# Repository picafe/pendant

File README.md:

# Bicolor LED Pendant

A pendant built from two PCBs: a 8×8 bicolor LED matrix module (red, orange, green) and controller board with battery charging, USB-C power, 5 V boost, and motion sensing.

## Why I made this

I had already been working on a 32×8 bicolor matrix module and wanted to try the Pendant YSWS before the deadline. An example on the pendant website inspired me to make a bicolor version with an orange fire-style pattern. Fitting the full matrix and controller on one 2/4 layer board was not the most possible, so my design splits into a display PCB and a pendant controller, which are connected with 2.54mm pitch pin headers (likely just male machine pin headers soldered on both sides, since they have a larger spacing to accomodate for the inductor). There is also an accelerometer to have potential particle motion simulation.

## Photos

### 3D model

### Schematic

**Controller**

**Matrix**

### PCB layouts

**Controller board**

**Matrix module**

## Connections

All signals between the two boards are carried on PCB-mounted 2.54 mm pin headers. No off-board wiring is required beyond a LiPo cell on the controller.

## Bill of materials

Prices are per-unit LCSC values; standard connector values are estimated.

### Controller PCB

| Ref | Qty | Value | LCSC | Unit | Extended |
|-----|-----|-------|------|------|----------|
| U3 | 1 | STM32C071G8U6 | C44521811 | $1.67 | $1.67 |
| U4 | 1 | TPS61022 | C915088 | $1.32 | $1.32 |
| U5 | 1 | LIS2DW12TR | C189624 | $1.25 | $1.25 |
| U1 | 1 | XC6206P332MR | C5446 | $0.102 | $0.10 |
| U6 | 1 | TP4056-42-ESOP8 | C16581 | $0.19 | $0.19 |
| L1 | 1 | FXL0530-1R0-M | C475517 | $0.17 | $0.17 |
| Q1, Q2, Q3 | 3 | BSS138W | C28646265 | $0.025 | $0.08 |
| D1 | 1 | BAT54CW | C22392482 | $0.035 | $0.04 |
| D2 | 1 | Red LED | C2286 | $0.009 | $0.01 |
| D3 | 1 | SS34 | C8678 | $0.030 | $0.03 |
| F1 | 1 | SMD1206B150TFT | C269120 | $0.03 | $0.03 |
| S1 | 1 | Tactile button | C720477 | $0.053 | $0.05 |
| J4 | 1 | USB-C receptacle | C18357552 | $0.08 | $0.08 |
| J1 | 1 | JST-SH 4-pin | - | $0.08 *(est.)* | $0.08 |
| J2, J3 | 2 | 4-pin pin socket | - | $0.05 *(est.)* | $0.10 |
| J5 | 1 | 2-pin pin socket | - | $0.03 *(est.)* | $0.03 |
| C9–C13 | 5 | 10 µF | C440198 | $0.069 | $0.35 |
| C1 | 1 | 4.7 µF | C19666 | $0.014 | $0.01 |
| C8 | 1 | 10 µF | C96446 | $0.021 | $0.02 |
| C3, C4, C7 | 3 | 100 nF | C14663 | $0.006 | $0.02 |
| C5 | 1 | 1 µF | C15849 | $0.008 | $0.01 |
| C6 | 1 | 1 µF | C28323 | $0.012 | $0.01 |
| C2 | 1 | 100 nF | C1525 | $0.004 | $0.00 |
| R10–R11, R8–R9 | 4 | 4.7 kΩ | C25900 | $0.004 | $0.02 |
| R4, R5 | 2 | 5.1 kΩ | C25905 | $0.004 | $0.01 |
| R2, R6 | 2 | 100 kΩ | C25741 | $0.004 | $0.01 |
| R1 | 1 | 750 kΩ | C23240 | $0.004 | $0.00 |
| R3 | 1 | 1 kΩ | C11702 | $0.004 | $0.00 |
| R7 | 1 | 10 kΩ | C25804 | $0.004 | $0.00 |
| R12 | 1 | 10 kΩ | C25744 | $0.004 | $0.00 |
| R13 | 1 | 120 Ω | C25079 | $0.004 | $0.00 |

**Controller subtotal: $5.71**

### Matrix PCB

| Ref | Qty | Value | LCSC | Unit | Extended |
|-----|-----|-------|------|------|----------|
| U1 | 1 | HT16K33A-28SSOP | C5444738 | $0.50 | $0.50 |
| LED1 | 1 | 8×8 bicolor LED matrix | - | $1.50 *(est.)* | $1.50 |
| R1–R3 | 3 | 47 kΩ | C25819 | $0.004 | $0.01 |
| C1 | 1 | 100 nF | C14663 | $0.006 | $0.01 |
| D1 | 1 | 1N4148WS | C2128 | $0.012 | $0.01 |
| J1, J2 | 2 | 4-pin pin socket | - | $0.05 *(est.)* | $0.10 |

**Matrix subtotal: $2.13**

### Total component cost

| Board | Subtotal |
|-------|----------|
| Controller | $5.71 |
| Matrix | $2.13 |
| **Grand total (1× each board)** | **$7.84** |

*Does not include PCB fabrication, shipping, LiPo battery, or assembly fees.*

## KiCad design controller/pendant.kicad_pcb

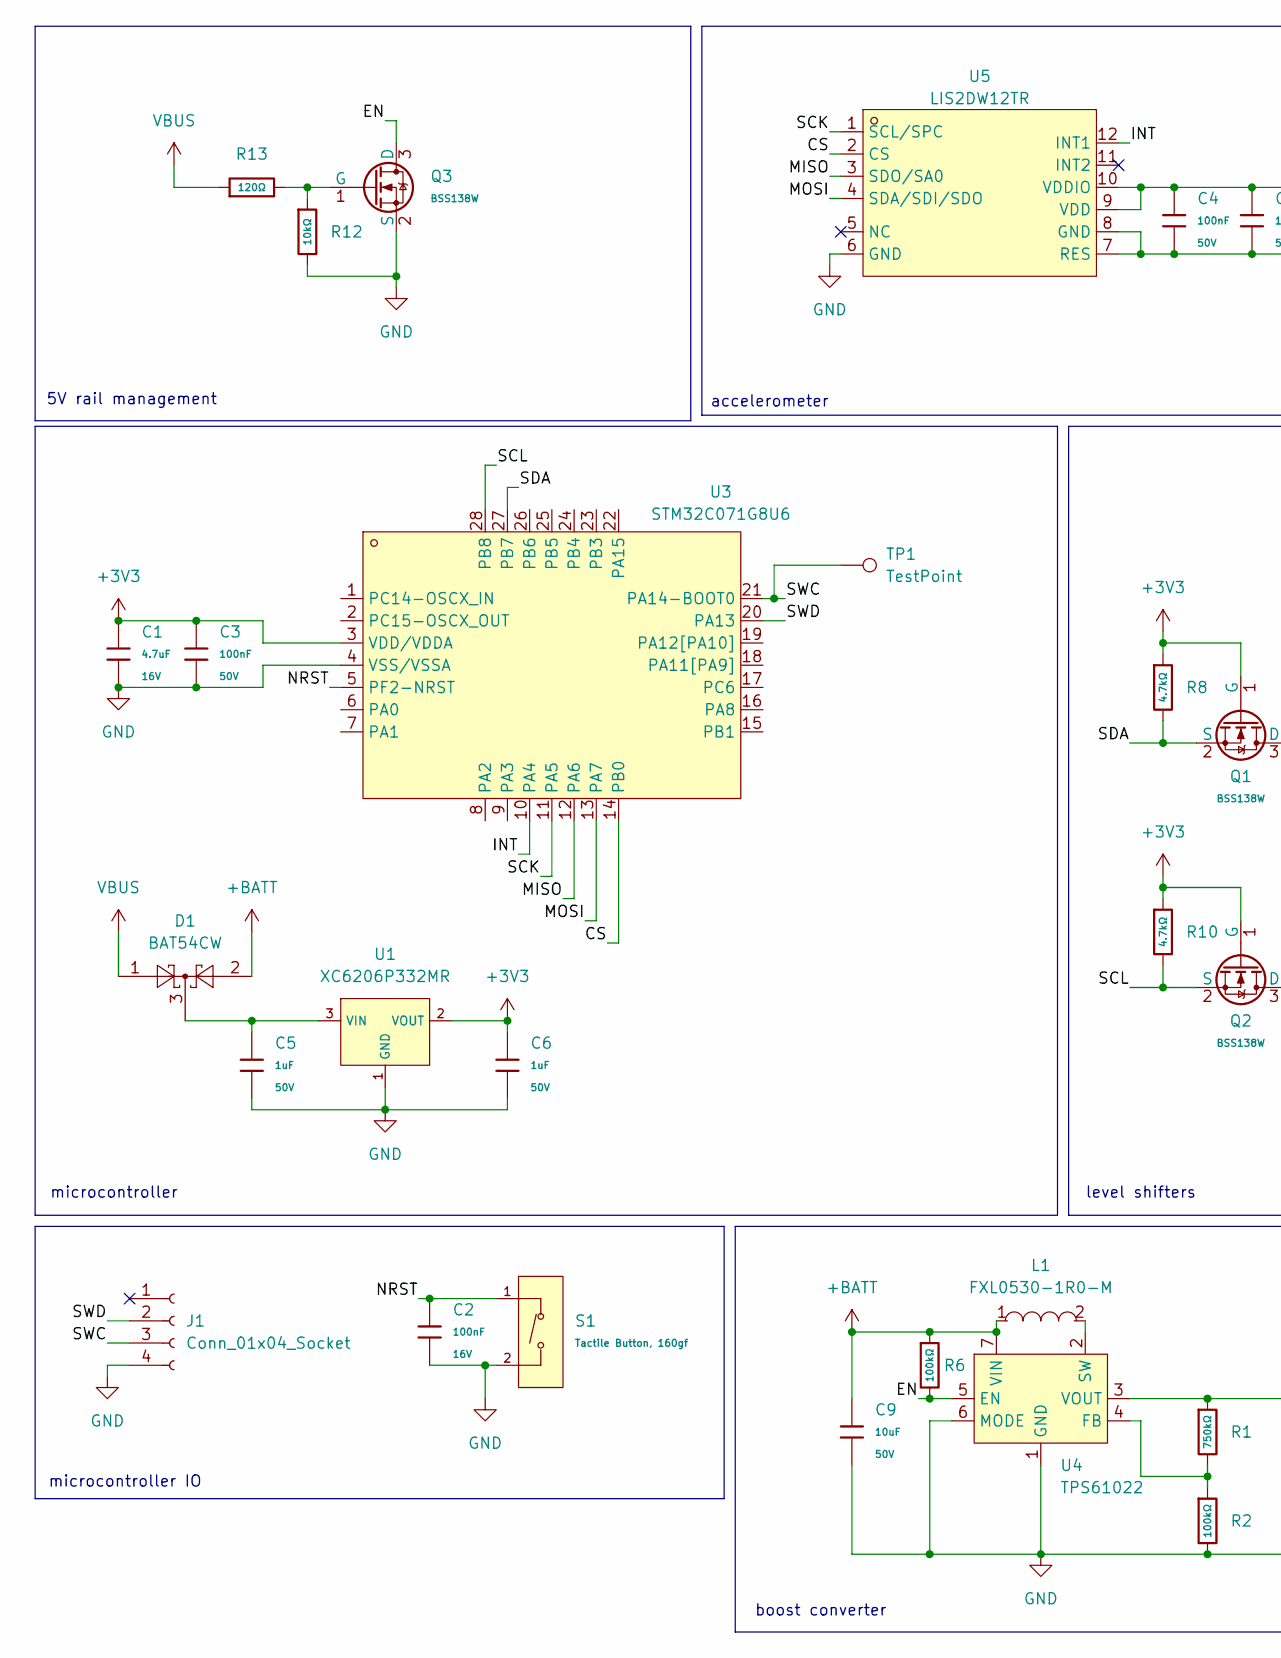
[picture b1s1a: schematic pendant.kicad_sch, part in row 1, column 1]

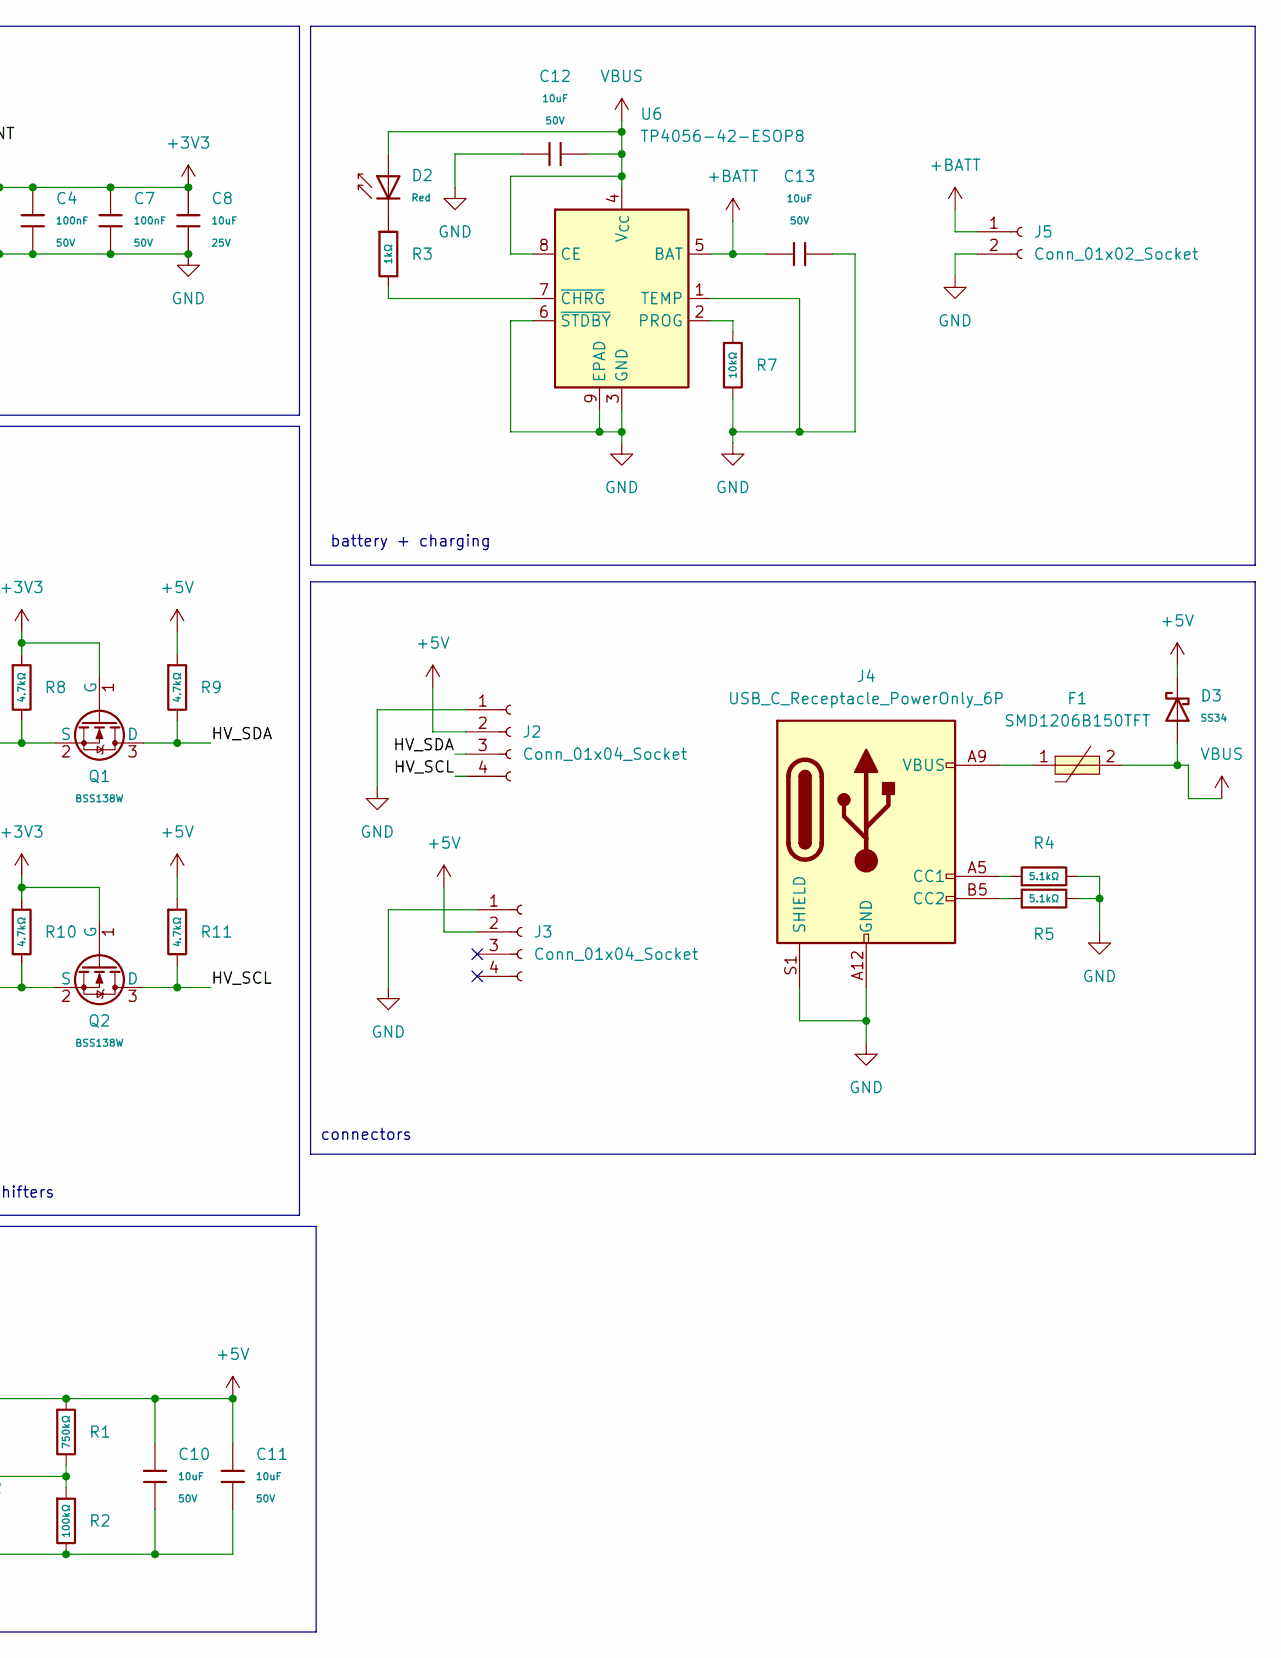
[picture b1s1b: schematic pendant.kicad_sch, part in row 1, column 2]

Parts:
C1: 4.7uF; C_0603; Voltage Rated 16V; Tolerance ±10%; Part CL10A475KO8NNNC; LCSC C19666
C2: 100nF; C_0402; Voltage Rated 16V; Tolerance ±10%; Part CL05B104KO5NNNC; LCSC C1525
C3, C4, C7: 100nF; C_0603; Voltage Rated 50V; Tolerance ±10%; Part CC0603KRX7R9BB104; LCSC C14663
C5: 1uF; C_0603; Voltage Rated 50V; Tolerance ±10%; Part CL10A105KB8NNNC; LCSC C15849
C6: 1uF; C_0805; Voltage Rated 50V; Tolerance ±10%; Part CL21B105KBFNNNE; LCSC C28323
C8: 10uF; C_0603; Voltage Rated 25V; Tolerance ±20%; Part CL10A106MA8NRNC; LCSC C96446
C9, C10, C11, C12, C13: 10uF; C_0805; Voltage Rated 50V; Tolerance ±10%; Part GRM21BR61H106KE43L; LCSC C440198
D1: BAT54CW; SOT-323_SC-70; LCSC C22392482
D2: Red; D_0603; Part KT-0603R; LCSC C2286
D3: SS34; D_SMA; Forward Voltage (Vf@If) 550mV@3A; Reverse Voltage (Vr) 40V; Part SS34; LCSC C8678
F1: SMD1206B150TFT; F1206; MPN SMD1206B150TFT; LCSC Part C269120
J1: Conn_01x04_Socket; JST_SH_SM04B-SRSS-TB_1x04-1MP_P1.00mm_Horizontal
J2, J3: Conn_01x04_Socket; PinSocket_1x04_P2.54mm_Vertical
J4: USB_C_Receptacle_PowerOnly_6P; USB-C-SMD_HX-TYPE-C-6PIN; LCSC C18357552
J5: Conn_01x02_Socket; PinSocket_1x02_P2.00mm_Vertical
L1: FXL0530-1R0-M; IND-SMD_L5.4-W5.2_FXL0530; MPN FXL0530-1R0-M; LCSC Part C475517
Q1, Q2, Q3: BSS138W; SOT-323_SC-70; Part BSS138W; LCSC C28646265
R1: 750kΩ; R_0603; Overload Voltage (Max) 75V; Tolerance ±1%; Part 0603WAF7503T5E; LCSC C23240
R2, R6: 100kΩ; R_0402; Overload Voltage (Max) 50V; Tolerance ±1%; Part 0402WGF1003TCE; LCSC C25741
R3: 1kΩ; R_0402; Overload Voltage (Max) 50V; Tolerance ±1%; Part 0402WGF1001TCE; LCSC C11702
R4, R5: 5.1kΩ; R_0402; Overload Voltage (Max) 50V; Tolerance ±1%; Part 0402WGF5101TCE; LCSC C25905
R7: 10kΩ; R_0603; Overload Voltage (Max) 75V; Tolerance ±1%; Part 0603WAF1002T5E; LCSC C25804
R8, R9, R10, R11: 4.7kΩ; R_0402; Overload Voltage (Max) 50V; Tolerance ±1%; Part 0402WGF4701TCE; LCSC C25900
R12: 10kΩ; R_0402; Overload Voltage (Max) 50V; Tolerance ±1%; Part 0402WGF1002TCE; LCSC C25744
R13: 120Ω; R_0402; Overload Voltage (Max) 50V; Tolerance ±1%; Part 0402WGF1200TCE; LCSC C25079
S1: Tactile Button, 160gf; SW_SPST_TS-1088-xR020; Voltage Rating (Dc) 12V; Part TS-1088-AR02016; LCSC C720477
TP1: TestPoint; TestPoint_Pad_D1.0mm
U1: XC6206P332MR; SOT-23-3; Output Voltage 3.3V; Dropout Voltage 680mV@(100mA); Part XC6206P332MR-G; LCSC C5446
U3: STM32C071G8U6; QFN-28_L4.0-W4.0-P0.50-TL; MPN STM32C071G8U6; LCSC Part C44521811
U4: TPS61022; Texas_RWU0007A_VQFN-7_2x2mm_P0.5mm; LCSC C915088
U5: LIS2DW12TR; LGA-12_L2.0-W2.0-P0.50-BL; MPN LIS2DW12TR; LCSC Part C189624
U6: TP4056-42-ESOP8; SOIC-8-1EP_3.9x4.9mm_P1.27mm_EP2.41x3.3mm_ThermalVias; LCSC C16581

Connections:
+3V3: C1.1, C3.1, C4.2, C6.1, C7.1, C8.1, Q1.1 (G), Q2.1 (G), R8.1, R10.1, U1.2 (VOUT), U3.3 (VDD/VDDA), U5.9 (VDD), U5.10 (VDDIO)
+5V: C10.1, C11.1, D3.1, J2.2, J3.2, R1.1, R9.1, R11.1, U4.3 (VOUT)
+BATT: C9.1, C13.1, D1.2, J5.1, L1.1, R6.1, U4.7 (VIN), U6.5 (BAT)
/CS: U3.14 (PB0), U5.2 (CS)
/EN: Q3.3 (D), R6.2, U4.5 (EN)
/HV_SCL: J2.4, Q2.3 (D), R11.2
/HV_SDA: J2.3, Q1.3 (D), R9.2
/INT: U3.10 (PA4), U5.12 (INT1)
/MISO: U3.12 (PA6), U5.3 (SDO/SA0)
/MOSI: U3.13 (PA7), U5.4 (SDA/SDI/SDO)
/NRST: C2.1, S1.1 (A), U3.5 (PF2-NRST)
/SCK: U3.11 (PA5), U5.1 (SCL/SPC)
/SCL: Q2.2 (S), R10.2, U3.28 (PB8)
/SDA: Q1.2 (S), R8.2, U3.27 (PB7)
/SWC: J1.3, TP1.1, U3.21 (PA14-BOOT0)
/SWD: J1.2, U3.20 (PA13)
GND: C1.2, C2.2, C3.2, C4.1, C5.2, C6.2, C7.2, C8.2, C9.2, C10.2, C11.2, C12.1, C13.2, J1.4, J2.1, J3.1, J4.A12 (GND), J4.B12 (GND), J4.S1 (SHIELD), J5.2, Q3.2 (S), R2.2, R4.2, R5.2, R7.2, R12.2, S1.2 (B), U1.1 (GND), U3.4 (VSS/VSSA), U4.1 (GND), U4.6 (MODE), U5.6 (GND), U5.7 (RES), U5.8 (GND), U6.1 (TEMP), U6.3 (GND), U6.6 (~STDBY), U6.9 (EPAD)
unnamed: D2.1, R3.1
unnamed: F1.1, J4.A9 (VBUS), J4.B9 (VBUS)
unnamed: J4.A5 (CC1), R4.1
unnamed: J4.B5 (CC2), R5.1
unnamed: Q3.1 (G), R12.1, R13.2
unnamed: C5.1, D1.3, U1.3 (VIN)
unnamed: R1.2, R2.1, U4.4 (FB)
unnamed: L1.2, U4.2 (SW)
unnamed: R7.1, U6.2 (PROG)
unnamed: R3.2, U6.7 (~CHRG)
VBUS: C12.2, D1.1, D2.2, D3.2, F1.2, R13.1, U6.4 (V_{CC}), U6.8 (CE)

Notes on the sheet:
boost converter
level shifters
connectors
battery + charging
accelerometer
microcontroller
5V rail management
microcontroller IO

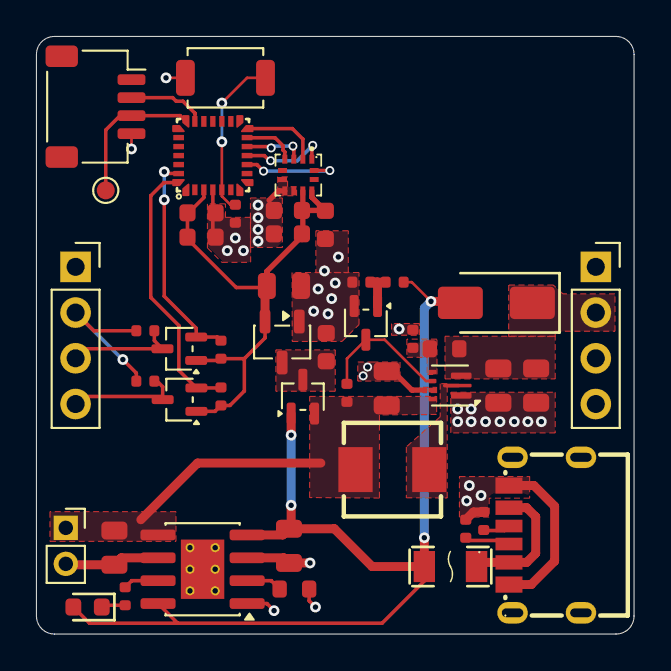
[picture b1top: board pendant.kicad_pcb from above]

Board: 4 copper layers, 33.2 x 33.2 mm, 46 parts (0 on the bottom side), 28 nets.

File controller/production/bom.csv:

Designator,Footprint,Quantity,Value,LCSC Part #
C1,C_0603,1,4.7uF,C19666
"C10, C11, C12, C13, C9",C_0805,5,10uF,C440198
C2,C_0402,1,100nF,C1525
"C3, C4, C7",C_0603,3,100nF,C14663
C5,C_0603,1,1uF,C15849
C6,C_0805,1,1uF,C28323
C8,C_0603,1,10uF,C96446
D1,SOT-323_SC-70,1,BAT54CW,C22392482
D2,D_0603,1,Red,C2286
D3,D_SMA,1,SS34,C8678
F1,F1206,1,SMD1206B150TFT,C269120
J1,JST_SH_SM04B-SRSS-TB_1x04-1MP_P1.00mm_Horizontal,1,Conn_01x04_Socket,
"J2, J3",PinSocket_1x04_P2.54mm_Vertical,2,Conn_01x04_Socket,
J4,USB-C-SMD_HX-TYPE-C-6PIN,1,USB_C_Receptacle_PowerOnly_6P,C18357552
J5,PinSocket_1x02_P2.00mm_Vertical,1,Conn_01x02_Socket,
L1,IND-SMD_L5.4-W5.2_FXL0530,1,FXL0530-1R0-M,C475517
"Q1, Q2, Q3",SOT-323_SC-70,3,BSS138W,C28646265
R1,R_0603,1,750kΩ,C23240
"R10, R11, R8, R9",R_0402,4,4.7kΩ,C25900
R12,R_0402,1,10kΩ,C25744
R13,R_0402,1,120Ω,C25079
"R2, R6",R_0402,2,100kΩ,C25741
R3,R_0402,1,1kΩ,C11702
"R4, R5",R_0402,2,5.1kΩ,C25905
R7,R_0603,1,10kΩ,C25804
S1,SW_SPST_TS-1088-xR020,1,"Tactile Button, 160gf",C720477
TP1,TestPoint_Pad_D1.0mm,1,TestPoint,
U1,SOT-23-3,1,XC6206P332MR,C5446
U3,QFN-28_L4.0-W4.0-P0.50-TL,1,STM32C071G8U6,C44521811
U4,Texas_RWU0007A_VQFN-7_2x2mm_P0.5mm,1,TPS61022,C915088
U5,LGA-12_L2.0-W2.0-P0.50-BL,1,LIS2DW12TR,C189624
U6,SOIC-8-1EP_3.9x4.9mm_P1.27mm_EP2.41x3.3mm_ThermalVias,1,TP4056-42-ESOP8,C16581

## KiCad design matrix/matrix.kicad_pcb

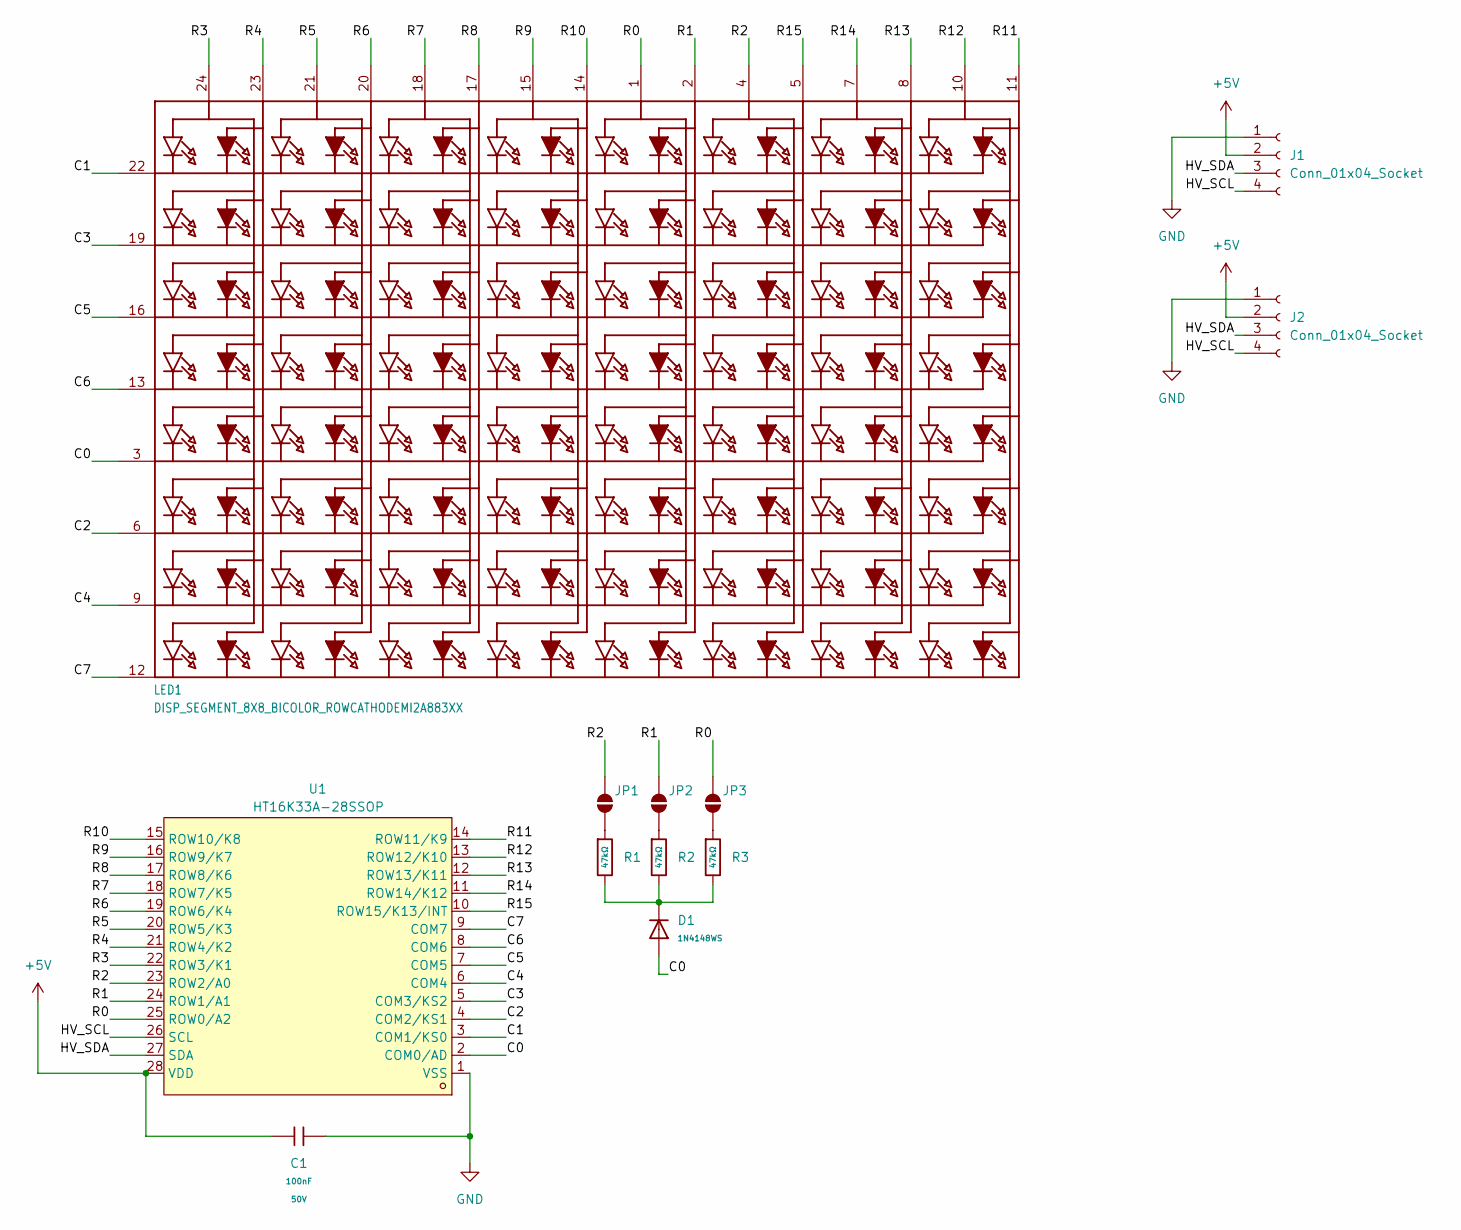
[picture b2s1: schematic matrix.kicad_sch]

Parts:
C1: 100nF; C_0603; Voltage Rated 50V; Tolerance ±10%; Part CC0603KRX7R9BB104; LCSC C14663
D1: 1N4148WS; D_SOD-323; Forward Voltage (Vf@If) 1.25V@150mA; Reverse Voltage (Vr) 100V; Part 1N4148WS; LCSC C2128
J1, J2: Conn_01x04_Socket; PinSocket_1x04_P2.54mm_Vertical
JP1, JP2, JP3: SolderJumper_2_Open; SolderJumper-2_P1.3mm_Open_RoundedPad1.0x1.5mm
LED1: DISP_SEGMENT_8X8_BICOLOR_ROWCATHODEMI2A883XX; SEGMENT_BICOL_BL-M12A883XX
R1, R2, R3: 47kΩ; R_0603; Overload Voltage (Max) 75V; Tolerance ±1%; Part 0603WAF4702T5E; LCSC C25819
U1: HT16K33A-28SSOP; SSOP-28_3.9x9.9mm_P0.635mm; LCSC Part C5444738

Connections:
+5V: C1.1, J1.2, J2.2, U1.28 (VDD)
/C0: D1.2, LED1.3 (K5), U1.2 (COM0/AD)
/C1: LED1.22 (K1), U1.3 (COM1/KS0)
/C2: LED1.6 (K6), U1.4 (COM2/KS1)
/C3: LED1.19 (K2), U1.5 (COM3/KS2)
/C4: LED1.9 (K7), U1.6 (COM4)
/C5: LED1.16 (K3), U1.7 (COM5)
/C6: LED1.13 (K4), U1.8 (COM6)
/C7: LED1.12 (K8), U1.9 (COM7)
/HV_SCL: J1.4, J2.4, U1.26 (SCL)
/HV_SDA: J1.3, J2.3, U1.27 (SDA)
/R0: JP3.2 (B), LED1.1 (A9), U1.25 (ROW0/A2)
/R1: JP2.2 (B), LED1.2 (A10), U1.24 (ROW1/A1)
/R2: JP1.2 (B), LED1.4 (A11), U1.23 (ROW2/A0)
/R3: LED1.24 (A1), U1.22 (ROW3/K1)
/R4: LED1.23 (A2), U1.21 (ROW4/K2)
/R5: LED1.21 (A3), U1.20 (ROW5/K3)
/R6: LED1.20 (A4), U1.19 (ROW6/K4)
/R7: LED1.18 (A5), U1.18 (ROW7/K5)
/R8: LED1.17 (A6), U1.17 (ROW8/K6)
/R9: LED1.15 (A7), U1.16 (ROW9/K7)
/R10: LED1.14 (A8), U1.15 (ROW10/K8)
/R11: LED1.11 (A16), U1.14 (ROW11/K9)
/R12: LED1.10 (A15), U1.13 (ROW12/K10)
/R13: LED1.8 (A14), U1.12 (ROW13/K11)
/R14: LED1.7 (A13), U1.11 (ROW14/K12)
/R15: LED1.5 (A12), U1.10 (ROW15/K13/INT)
GND: C1.2, J1.1, J2.1, U1.1 (VSS)
unnamed: D1.1, R1.2, R2.2, R3.2
unnamed: JP1.1 (A), R1.1
unnamed: JP2.1 (A), R2.1
unnamed: JP3.1 (A), R3.1

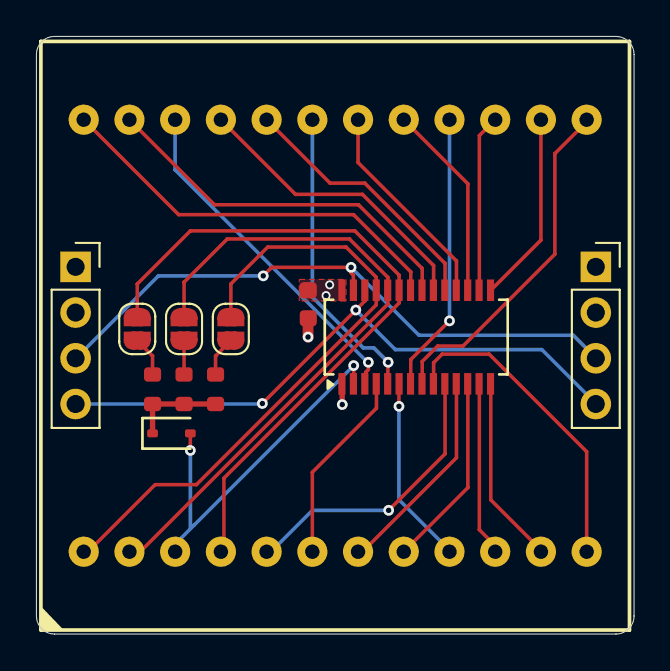
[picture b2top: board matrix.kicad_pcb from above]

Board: 4 copper layers, 33.2 x 33.2 mm, 12 parts (0 on the bottom side), 32 nets.

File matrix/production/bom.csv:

Designator,Footprint,Quantity,Value,LCSC Part #
C1,C_0603,1,100nF,C14663
D1,D_SOD-323,1,1N4148WS,C2128
"J1, J2",PinSocket_1x04_P2.54mm_Vertical,2,Conn_01x04_Socket,
LED1,SEGMENT_BICOL_BL-M12A883XX,1,DISP_SEGMENT_8X8_BICOLOR_ROWCATHODEMI2A883XX,
"R1, R2, R3",R_0603,3,47kΩ,C25819
U1,SSOP-28_3.9x9.9mm_P0.635mm,1,HT16K33A-28SSOP,C5444738

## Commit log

2026-06-20 init
2026-06-20 fix: update library
2026-06-21 feat: journal, pcb, prod files
2026-06-21 fix: typo
2026-06-21 fix: readme
2026-06-21 update: journal
2026-06-26 feat: power fixes
2026-06-29 feat: update pcb + readme
2026-06-29 feat: other changes
